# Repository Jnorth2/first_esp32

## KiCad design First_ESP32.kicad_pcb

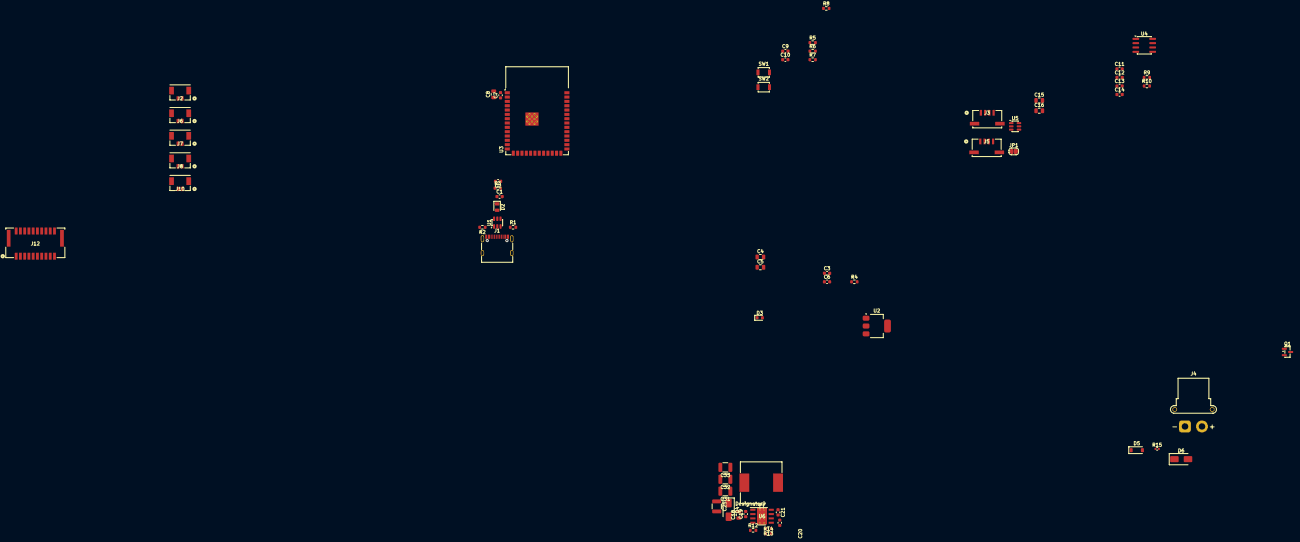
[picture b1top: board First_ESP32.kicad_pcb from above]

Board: 2 copper layers, 64 parts (0 on the bottom side), 49 nets, no tracks yet.

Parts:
C1, C2: 4u7; C_0603_1608Metric
C3, C6, C7, C9, C10, C21: 100n; C_0603_1608Metric
C4, C5, C15, C16: 10uF; C_0805_2012Metric
C8, C18: 10u; C_0805_2012Metric
C11, C12: 100nF; C_0603_1608Metric
C13: 4.7nF; C_0603_1608Metric
C14, C20: 1uF; C_0603_1608Metric
C19: 220n; C_0603_1608Metric
C25, C31, C32, C33: 22uF; C_1210_3225Metric
D2: 1N5819HW-7-F; D_0805_2012Metric
D3: LED; LED_0603_1608Metric
D4: SMAJ6.0A (6.0V TVS); D_SMA
D5: MMSZ5245B (15V); D_SOD-123
D6: SMAJ33A (33V TVS); D_SMA
J1: USB_C_Receptacle_USB2.0_16P; USB_C_Receptacle_G-Switch_GT-USB-7010ASV
J2, J6, J7, J8, J10: 5055670271; CONN_505567_02_MOL
J3, J5: SM04B-GHS-TB; CONN_SM04B-GHS-TB_JST
J4: XT30 (right-angle); AMASS_XT30PW-F_1x02_P2.50mm_Horizontal
J12: 5054482071; CONN_505448_20_MOL
JP1: SolderJumper_2_Open; SolderJumper-2_P1.3mm_Open_RoundedPad1.0x1.5mm
L1: 8u; L_Wurth_WE-PD-1260
Q1: DMP3098L-7; SOT-23
R1, R2: 5k1; R_0603_1608Metric
R3: 0R; R_0603_1608Metric
R4, R6, R8: 100; R_0603_1608Metric
R5, R7: 10k; R_0603_1608Metric
R9, R10: 60; R_0603_1608Metric
R12, R14: 100k; R_0603_1608Metric
R13: 24.9k; R_0603_1608Metric
R15: 10k; R_0402_1005Metric
SW1, SW2: B3U-1000P; SW_SPST_B3U-1000P
U1: USBLC6-2SC6; SOT-23-6
U2: AMS1117-3.3; SOT-223-3_TabPin2
U3: ESP32-S3-WROOM-1
U4: TJA1051T/3; SOIC-8_3.9x4.9mm_P1.27mm
U5: AP3602A; SOT-23-6
U6: LMR33630; DDA0008J

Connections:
+3V3: C5.1, C6.1, C7.1, C8.1, C12.1, C15.1, J12.3, J12.17, R4.1, R5.1, R7.1, U2.2 (VO), U3.2 (3V3), U4.5 (VIO), U5.3 (~SHDN), U5.5 (VIN)
+5V: C2.1, C3.1, C4.1, C25.1, C31.1, C32.1, C33.1, D4.1 (K), J3.1, J5.1, J7.1, J8.1, J10.1, J12.1, J12.19, L1.2, R3.2, R14.1, U2.3 (VI)
+5V_CAN: C11.1, C16.1, U4.3 (VCC), U5.1 (5VO)
+24V: C18.1, C19.1, D6.1 (K), Q1.3 (D), U6.2 (VIN), U6.3 (EN)
/ESP32-S3/D+: J1.A6 (D+), J1.B6 (D+), U1.3 (I/O2)
/ESP32-S3/D-: J1.A7 (D-), J1.B7 (D-), U1.1 (I/O1)
BOOT: C10.1, R8.2, U3.27 (IO0)
CANH: J3.2, J5.2, JP1.1, U4.7 (CANH)
CANL: J3.3, J5.3, R10.2, U4.6 (CANL)
CAN_RX: U3.5 (IO5), U4.4 (RXD)
CAN_TX: U3.4 (IO4), U4.1 (TXD)
EN: C9.1, R6.2, U3.3 (EN)
GND: C1.2, C2.2, C3.2, C4.2, C5.2, C6.2, C7.2, C8.2, C9.2, C10.2, C11.2, C12.2, C13.2, C15.2, C16.2, C18.2, C19.2, C20.2, C25.2, C31.2, C32.2, C33.2, D3.1 (K), D4.2 (A), D6.2 (A), J1.A1 (GND), J1.A12 (GND), J1.B1 (GND), J1.B12 (GND), J1.S1 (SHIELD), J3.4, J4.1, J5.4, J7.2, J8.2, J10.2, J12.2, J12.4, J12.18, J12.20, R1.2, R2.2, R13.2, R15.2, SW1.1, SW2.1, U1.2 (GND), U2.1 (GND), U3.1 (GND), U3.40 (GND), U3.41 (GND), U4.2 (GND), U4.8 (S), U5.2 (GND), U6.1 (PGND)
GPIO1: J12.7, U3.39 (IO1)
GPIO3: J12.8, U3.15 (IO3)
GPIO11: J12.9, U3.19 (IO11)
GPIO12: J12.10, U3.20 (IO12)
GPIO13: J12.11, U3.21 (IO13)
GPIO14: J12.12, U3.22 (IO14)
GPIO15: J12.13, U3.8 (IO15)
GPIO16: J12.14, U3.9 (IO16)
GPIO39: J12.15, U3.32 (IO39)
GPIO40: J12.16, U3.33 (IO40)
unnamed: C13.1, R9.2, R10.1
unnamed: C1.1, D2.1 (K), R3.1
unnamed: D3.2 (A), R4.2
unnamed: D5.2 (A), Q1.1 (G), R15.1
unnamed: D5.1 (K), J4.2, Q1.2 (S)
unnamed: J1.A5 (CC1), R2.1
unnamed: J1.B5 (CC2), R1.1
unnamed: JP1.2, R9.1
unnamed: R5.2, R6.1, SW1.2
unnamed: R7.2, R8.1, SW2.2
unnamed: C14.1, U5.6 (C+)
unnamed: C14.2, U5.4 (C-)
unnamed: C21.2, U6.7 (BOOT)
unnamed: R13.1, R14.2, U6.5 (FB)
unnamed: R12.1, U6.4 (PG)
unnamed: C21.1, L1.1, U6.8 (SW)
unnamed: C20.1, R12.2, U6.6 (VCC)
RX: J12.6, U3.36 (RXD0)
SCL_1: J2.2, U3.7 (IO7)
SCL_2: J6.2, U3.18 (IO10)
SDA_1: J2.1, U3.6 (IO6)
SDA_2: J6.1, U3.17 (IO9)
TX: J12.5, U3.37 (TXD0)
USB_D+: U1.4 (I/O2), U3.14 (USB_D+)
USB_D-: U1.6 (I/O1), U3.13 (USB_D-)
VBUS: D2.2 (A), J1.A4 (VBUS), J1.A9 (VBUS), J1.B4 (VBUS), J1.B9 (VBUS), U1.5 (VBUS)
